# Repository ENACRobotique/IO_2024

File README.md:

# IO_2024
Carte et Soft pour les actionneurs de la coupe 2024 ( recyclage de la carte servo testeur )

Board : [Nucleo L432KC](https://www.st.com/en/evaluation-tools/nucleo-l432kc.html#documentation)

Depuis le haut niveau envoyer en utilisant l'UART un mesage de la forme "actionneur valeur\n"

Exemple pour tourner le servo 2 a la valeur 1200 en utlisant pyserial on peut faire write(b'2 1200\n')

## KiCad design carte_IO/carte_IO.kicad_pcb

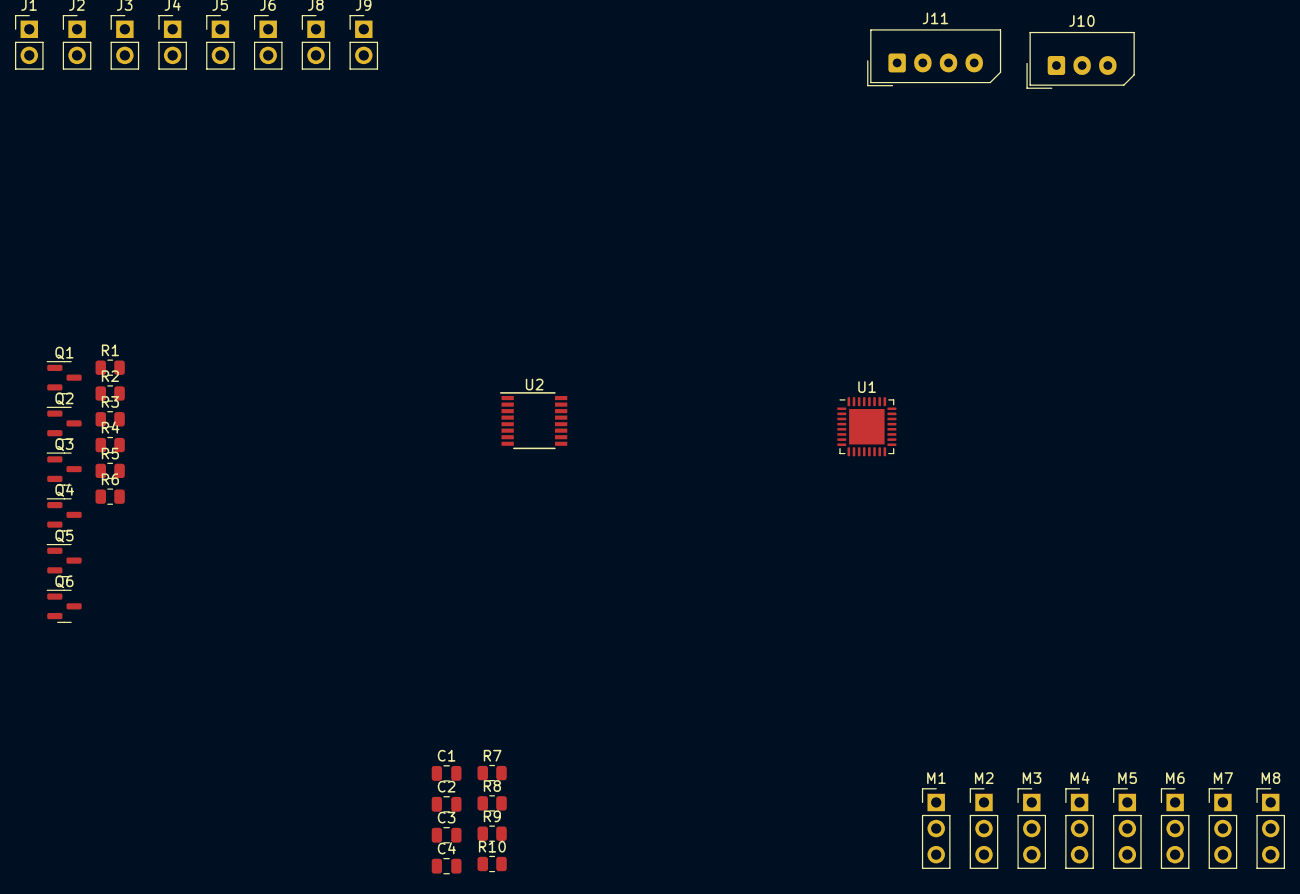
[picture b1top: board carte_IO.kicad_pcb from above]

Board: 2 copper layers, 40 parts (0 on the bottom side), 29 nets, no tracks yet.

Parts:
C1, C2: C_Polarized; C_0805_2012Metric
C3, C4: 10µF; C_0805_2012Metric
J1, J2, J3, J4, J5, J6, J8, J9: Conn_01x02_Pin; PinHeader_1x02_P2.54mm_Vertical
J10: AX12; Molex_SPOX_5267-03A_1x03_P2.50mm_Vertical
J11: AX12; Molex_SPOX_5267-04A_1x04_P2.50mm_Vertical
M1, M2, M3, M4, M5, M6, M7, M8: Motor_Servo; PinHeader_1x03_P2.54mm_Vertical
Q1, Q2, Q3, Q4, Q5, Q6: IRLML6344; SOT-23
R1, R2, R3, R4, R5, R6: 10k; R_0805_2012Metric
R7, R8, R9, R10: R; R_0805_2012Metric
U1: STM32L432KCUx; QFN-32-1EP_5x5mm_P0.5mm_EP3.45x3.45mm
U2: TCA9554DBQ; SSOP-16_3.9x4.9mm_P0.635mm

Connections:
+3.3V: U1.1 (VDD), U1.5 (VDDA), U1.17 (VDD)
+5V: J10.1, J11.1, M1.2 (+), M2.2 (+), M3.2 (+), M4.2 (+), M5.2 (+), M6.2 (+), M7.2 (+), M8.2 (+), U2.16 (VDD)
+12V: J1.2, J2.2, J3.2, J4.2, J5.2, J6.2, Q1.3 (D), Q2.3 (D), Q3.3 (D), Q4.3 (D), Q5.3 (D), Q6.3 (D)
AIMANT_1: Q4.1 (G), R1.2, U2.4 (P0)
AIMANT_2: Q3.1 (G), R2.2, U2.5 (P1)
AIMANT_3: Q1.1 (G), R3.2, U2.6 (P2)
AIMANT_4: Q5.1 (G), R5.2, U2.7 (P3)
AIMANT_5: Q2.1 (G), R4.2, U2.9 (P4)
AIMANT_6: Q6.1 (G), R6.2, U2.10 (P5)
AX12: J10.3, U1.29 (PB6), U1.30 (PB7)
FDC_1: J8.1, U2.11 (P6)
FDC_2: J9.1, U2.12 (P7)
GND: C1.2, C2.2, C3.2, C4.2, J1.1, J2.1, J3.1, J4.1, J5.1, J6.1, J8.2, J9.2, J10.2, J11.2, M1.3 (-), M2.3 (-), M3.3 (-), M4.3 (-), M5.3 (-), M6.3 (-), M7.3 (-), M8.3 (-), Q1.2 (S), Q2.2 (S), Q3.2 (S), Q4.2 (S), Q5.2 (S), Q6.2 (S), R1.1, R2.1, R3.1, R4.1, R5.1, R6.1, R7.2, R9.2, U2.8 (GND)
unnamed: U1.16 (VSS), U1.32 (VSS), U1.33 (VSS)
unnamed: R7.1, R8.2
unnamed: C2.1, R8.1
unnamed: R9.1, R10.2
unnamed: C4.1, R10.1
PANO_BRAS: M7.1 (PWM), U1.12 (PA6)
PANO_ROUE: M8.1 (PWM), U1.9 (PA3)
PINCE_1: M1.1 (PWM), U1.6 (PA0)
PINCE_2: M2.1 (PWM), U1.7 (PA1)
PINCE_3: M3.1 (PWM), U1.18 (PA8)
PINCE_4: M4.1 (PWM), U1.19 (PA9)
PINCE_5: M5.1 (PWM), U1.20 (PA10)
PINCE_6: M6.1 (PWM), U1.21 (PA11)
RX: J11.4, U1.25 (PA15)
TX: J11.3, U1.8 (PA2)
VCC: C1.1, C3.1

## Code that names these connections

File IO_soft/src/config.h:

#define SERVO1_PIN PB0
#define SERVO2_PIN PB1
#define SERVO3_PIN PA8
#define SERVO4_PIN PA6
#define SERVO5_PIN PA3
#define SERVO6_PIN PB6

#define AX_left 5
#define AX_right 1
#define AX_SPEED 300

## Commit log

2024-01-19 debut carte
2024-01-25 quelques connections
2024-02-02 move to lk32KC & add gitignore
2024-02-08 some instructions
2024-02-08 instruction
2024-02-19 1,2,3,4,5,6
2024-02-19 Test servo et aimant check
2024-02-22 config + tests demo ok
2024-02-29 values correction
2024-04-15 config nucleo
2024-04-16 update config
2024-04-16 IO fonctionnel
